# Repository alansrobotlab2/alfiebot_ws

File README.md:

# 🤖 Alfiebot Workspace

<div align="center">

**A ROS2 Jazzy workspace for an intelligent, interactive humanoid robot**

</div>

---

## 📋 Overview

Alfiebot is a conversational humanoid robot built on ROS2 Jazzy, featuring voice interaction, LLM-powered intelligence, and expressive servo-controlled movements. The platform integrates automatic speech recognition (ASR), large language model (LLM) processing, text-to-speech (TTS), and sophisticated motor control through micro-ROS firmware.

### Key Features

- 🎤 **Voice Interaction** - Real-time speech recognition and natural language understanding
- 🧠 **LLM Integration** - Powered by modern language models for intelligent conversations
- 🔊 **Text-to-Speech** - Natural voice synthesis for robot responses
- ⚙️ **Motor Control** - Servo-based articulation with Waveshare serial bus servos
- 📡 **Micro-ROS** - Efficient real-time communication with embedded firmware
- 🌐 **Network Management** - Built-in WiFi hotspot capabilities via Alfienet

---

## 🗂️ Package Structure

```
alfiebot_ws/
├── src/
│   ├── alfie_agent/       # High-level behavioral control and orchestration
│   ├── alfie_asr/         # Automatic speech recognition node
│   ├── alfie_back/        # Backend services and utilities
│   ├── alfie_bringup/     # Launch files and system startup configuration
│   ├── alfie_firmware/    # Micro-ROS firmware for embedded systems
│   ├── alfie_llm/         # Large language model integration
│   ├── alfie_mic/         # Microphone interface and audio capture
│   ├── alfie_msgs/        # Custom ROS2 message and service definitions
│   ├── alfie_tools/       # Development and debugging tools (servotool, etc.)
│   └── alfie_tts/         # Text-to-speech synthesis node
└── alfienet/              # WiFi hotspot and network management scripts
```

---

## 🚀 Quick Start

### Prerequisites

- NVIDIA Jetson device (tested on Jetson Orin series)
- ROS2 Jazzy
- Ubuntu 24.04 (JetPack 7)

### Setup

For detailed environment setup and dependencies, see **[SETUP.md](SETUP.md)**.

```bash
# Clone the repository
git clone https://github.com/alansrobotlab2/alfiebot_ws.git
cd alfiebot_ws

# Install dependencies
rosdep install --from-paths src --ignore-src -r -y

# Build the workspace
colcon build --symlink-install

# Source the workspace
source install/setup.zsh
```

### Running Alfiebot

```bash
# Launch the complete system
ros2 launch alfie_bringup alfiebot.launch.py

# Or launch individual components as needed
ros2 run alfie_asr asr_node
ros2 run alfie_llm llm_node
ros2 run alfie_tts tts_node
```

---

## 🛠️ Development Status

### Active Tasks

- [ ] Troubleshoot micro ros agent locking out usb when quitting launchfile
- [ ] Evaluate BEST_EFFORT vs RELIABLE QoS for core topics
- [ ] Debug message/video lag after overnight operation
- [ ] Investigate `alfie_mic` crash issue (related to reset step?)
- [ ] Benchmark Foxglove Bridge performance (on-device vs off-device)
- [ ] Fix ServoTool2 memory offset bug affecting EEPROM writes
- [ ] Add rate limiting to ServoTool slider (target: 20Hz)
- [ ] Implement min/max value constraints in ServoTool UI
- [ ] Add raw/degrees/radians unit selector to ServoTool I/O

### Modeling & Simulation

- [ ] Create simplified OnShape CAD model
- [ ] Export URDF for Foxglove Studio visualization
- [ ] Export model to NVIDIA Omniverse

### Hardware Development

- [ ] Build teleoperation rig with Teensy 4.2
- [ ] Implement "high five" gesture interaction

#### Upcoming Hardware Improvements

- [ ] Install dual antennas on head with body extensions
- [ ] Replace 6.6ft USB-C cable with 5ft version
- [ ] Upgrade shoulder bearings

#### Completed Hardware Updates ✅

- ✅ Installed smaller diameter middle wheel inserts (reduced turn jiggle)
- ✅ Replaced with quieter case fans in base
- ✅ Added wiring harness slack for 180° head rotation
- ✅ Centered Jetson for improved airflow

---

## 🔮 Future Roadmap

### Hardware Evolution

- **Base Redesign** - Lower-mounted drive wheels or omniwheel configuration
- **Autonomous Charging** - Docking station with automatic charge detection
- **Cable Management** - Cleaner internal wiring layout

### Software Enhancements

- Advanced behavioral planning and decision-making
- Multi-modal interaction (vision + voice)
- Cloud integration for knowledge updates
- Improved power management and battery monitoring

---

## 📚 Documentation

- **[SETUP.md](SETUP.md)** - Detailed installation and configuration guide
- **[Firmware README](src/alfie_firmware/README.md)** - Micro-ROS firmware documentation
- **[MKS-SERVO42C_1.0.md](MKS-SERVO42C_1.0.md)** - Servo motor documentation
- **[alfienet/](alfienet/)** - Network configuration documentation

---

## 🤝 Contributing

Contributions are welcome! This is an active research and development project.

---

## 📄 License

This project is licensed under the Apache License 2.0 - see the [LICENSE](LICENSE) file for details.

---

## 👤 Maintainer

**Alan's Robot Lab**  
📧 alansrobotlab@gmail.com  
🔗 [GitHub](https://github.com/alansrobotlab2)

---

<div align="center">
  <sub>Built with ❤️ and ROS2</sub>
</div>

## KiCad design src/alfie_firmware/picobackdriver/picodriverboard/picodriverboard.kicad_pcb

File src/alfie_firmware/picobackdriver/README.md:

# Pico Back Driver Board

Firmware for the Alfie robot's back lift — a belt-driven linear actuator on a
Waveshare RP2040 Zero, driven by a DRV8876 H-bridge and controlled over
micro-ROS.

Gen2 hardware. The gen1 TB6612FNG is gone; so is most of what the previous
revision of this document said about it.

---

## Hardware

| | |
|---|---|
| **MCU** | Waveshare RP2040 Zero (serial `5303284740EC7D9C` → `/dev/ttyAlfieB`) |
| **Driver** | DRV8876 (3.5 A, 44.3 °C/W, integrated current sense + fault reporting) |
| **Motor** | JGB37-520B, **56:1**, 178 rpm @ 12 V, 11 PPR quadrature encoder (fitted 2026-10-25, replacing the interim 90:1 / 110 rpm) |
| **Transmission** | 20T 2GT pulley (2 mm pitch, 40 mm circumference), GT2 belt |
| **IMU** | BNO085 on I2C0 |
| **Status LED** | WS2812B on GP16 |
| **Comms** | micro-ROS over USB CDC @ 1,000,000 baud |

### Pin map

| GPIO | Signal | Notes |
|---|---|---|
| GP28 | `EN` | PWM, 24 kHz |
| GP27 | `PH` | direction — `MOTOR_PH_UP = LOW` (56:1 motor) |
| GP26 | `PMODE` | driven **LOW** for PH/EN mode. Never leave floating |
| GP15 | `nSLEEP` | HIGH = active |
| GP7 | `nFAULT` | open-drain input, internal pull-up |
| GP3 / GP2 | `ENC_A` / `ENC_B` | quadrature, both on CHANGE |
| GP1 | `LIMIT_SW` | bottom limit, **normally closed → HIGH = triggered** |
| GP12 / GP13 | I2C0 SDA / SCL | BNO085 |
| GP11 | IMU reset | |
| GP16 | WS2812B | |

Free: GP0, GP4, GP5, GP6, GP8, GP9, GP10, GP14, GP17–22.

### DRV8876 configuration

| Pin | State | Why |
|---|---|---|
| `PMODE` | driven LOW from GP26 | PH/EN mode. Floating = independent half-bridge, which **inverts the down duty** on a gravity-loaded axis |
| `IMODE` | 20 kΩ to GND (level 2) | Only the overcurrent response still matters: **auto-retry**, not latch-off |
| `VREF` | tied to 3.3 V | Only needs to be above GND now |
| `IPROPI` / `CS` | **strapped to GND** | Disables internal current regulation, datasheet §7.3.3.2 |

**Current regulation is deliberately disabled.** The ITRIP chopper was clamping
below the current required to lift, so the actuator could not rise at any duty.
Overcurrent protection (3.5–5.5 A, 2 ms auto-retry) and thermal shutdown are
separate silicon and remain active — the part is still self-protecting.

With the chopper gone, **`VELOCITY_PID_OUTPUT_LIMIT` is the only thing bounding
motor current.** See `config.h`, "WHY THERE IS NO CURRENT TRIP".

---

## Calibrated constants

> **56:1 fitted 2026-10-25.** The constants below are the 56:1 values, rescaled
> from the 90:1 calibration by gearbox ratio. They are not yet confirmed on
> hardware. The performance table and its fit are 90:1 measurements. Re-run
> `position_test.cpp` calibration and the duty sweep, and verify encoder phasing
> and PH polarity by hand before the first powered move.

```
GEAR_RATIO              56.0        56:1 datasheet (90:1 calibrated to 90.1 against datasheet 90)
ENCODER_COUNTS_PER_METER 61,600     = 11 PPR × 4 × 56 / 0.040 m
counts per mm           61.6        350 mm = 21,560 counts
ACTUATOR_MAX_POSITION   0.350 m     real stroke from the limit switch
```

At 90:1, two independent checks agreed: the count calibration lands within 0.1% of the
geometric model, and the measured voltage-speed slope (5.82 mm/s per volt) is
within 5% of the theoretical 6.11 for 110 rpm through a 40 mm pulley.

### Measured performance (90:1)

At 56:1 the scaled fit is `v = 9.42 × (V_applied − 2.41)` mm/s: ~66 mm/s at
duty 200 and ~75 mm/s at duty 220, unmeasured.

| duty | speed (up) | 350 mm | stall current |
|---|---|---|---|
| 160 | 35.1 mm/s † | 10.0 s | 2.28 A |
| 200 | 46.1 mm/s | 7.7 s | 2.85 A |
| **220** ← ceiling | **51.5 mm/s** | **6.9 s** | 3.14 A |
| 245 | 58.4 mm/s † | 6.0 s | 3.50 A ← OCP floor |

† extrapolated from the measured fit `v = 5.82 × (V_applied − 1.50)` mm/s;
duty 200 and 220 are measured full-stroke runs.

Descent is gravity-assisted and ~35% faster: 69.7 mm/s at duty 220.

Running current is **~0.45 A** (from the voltage-speed intercept) — well under
the motor's 1.0 A continuous rating, and ~0.14 W in the driver. The drive is
lightly loaded.

The duty ceiling of 220 is set by **OCP margin**, not thermals: a dead stall
draws 3.14 A, 10% under the DRV8876's 3.5 A trip point, so a jam is answered by
the firmware stall detector rather than by driver retry chatter. 245 is the hard
ceiling on the ceiling.

---

## Control architecture

Dual-core, cascaded control.

- **Core 0** — peripherals: motor, encoder ISRs, IMU, limit switch, LED. Control
  loop at **500 Hz** (`CONTROL_LOOP_PERIOD_MS = 2`).
- **Core 1** — micro-ROS state machine at a drift-free **50 Hz**.

```
BackCmd.position ──► position error ──► × POSITION_KP (12) ──► desired velocity
                                                                      │
  BackCmd.velocity (a LIMIT) and √(2·a·|e|) braking curve ──► clamp ◄─┘
                                                     │
                            MAX_ACTUATOR_ACCELERATION ▼ ramp
                                                     │
                     encoder velocity ──► applyVelocityPID ──► PWM ──► DRV8876
```

**`BackCmd.velocity` is a maximum, not a setpoint.** Position is the command;
velocity and acceleration are constraints on how it gets there. Leaving either
at 0 means "use the maximum": GR00T's action publisher sends position only, and
before 2026-10-25 a 0 acceleration froze the ramp so the back never moved.

The braking curve caps speed at what the commanded acceleration can shed before
the target, so slow ramps (VR teleop uses 0.1 m/s²) land without overshoot.

Measured with GR00T-style position-only commands at 15 Hz (`POSITION_KP` 12,
1 mm tolerance): steps of 3-20 mm land within 0.1-0.7 mm in 0.12-0.54 s with no
overshoot; a 31 mm/s sine lags 2.3 mm on average (v / POSITION_KP); full strokes
take 7.3 s with under 0.7 mm overshoot.

### Gains and limits

```
VELOCITY_FF_UP_OFFSET       78        feedforward: up duty = 78 + 2.5 × v[mm/s] + friction
VELOCITY_FF_UP_GAIN         2500      counts per m/s
VELOCITY_FF_DOWN_OFFSET     -13       feedforward: down duty = -13 + 2.0 × v[mm/s] - friction (v < 0)
VELOCITY_FF_DOWN_GAIN       2000      counts per m/s
VELOCITY_FF_FRICTION_SLOPE  40        friction = 40 counts/m × (height − 0.160 m), opposing motion
VELOCITY_PID_KP             3000.0    PWM counts per m/s of error, trims the feedforward
VELOCITY_PID_KI             3000.0
VELOCITY_PID_KD             0.0       disabled
VELOCITY_PID_OUTPUT_LIMIT   220       duty ceiling = current ceiling
VELOCITY_PID_INTEGRAL_LIMIT 0.025     KI × limit = 75 counts of trim
MAX_ACTUATOR_VELOCITY       0.048 m/s measured on the 56:1
MAX_ACTUATOR_ACCELERATION   0.35 m/s²
MIN_PWM_UPWARD              100       floor, commanded direction only (re-measured on the 56:1)
MIN_PWM_DOWNWARD            20        gravity assists
POSITION_TOLERANCE_M        0.001     brake inside this
POSITION_KP                 12.0      outer loop gain (1/s)
```

Feedforward carries the load (56:1 tune, 2026-10-25); the PID only trims it.
Friction rises with height in both directions (repeatable, ~±5 counts across
the stroke), so the feedforward includes a height term. Velocity is the count
difference over a 20 ms window timed in `micros()`.

⚠️ **The load drifts warm.** After ~2 h of cycling the same speeds needed ~30
more counts of duty (board 41 → 50 °C, motor and gearbox warm), and 48 mm/s up
pinned at the 220 ceiling. The feedforward was fitted cool; the integral absorbs
up to 75 counts of drift.
Step response 20-48 mm/s up and down: rise 240-450 ms, steady-state error
within ±1.5%, 2-5% ripple. A full 0 -> 340 mm stroke takes 8.2 s.

Inside `POSITION_TOLERANCE_M` with the ramp at rest the bridge simply brakes
(the short brake holds the 56:1 with no measurable sag). Before that, encoder
noise was floored into continuous +100 / -20 pulses at every hold. Floors apply
only in the commanded direction, and the integral resets when it flips.

---

## Safety

| Detector | Trips on | Recovery |
|---|---|---|
| **Stall** | duty above `STALL_PWM_THRESHOLD` with no motion for 250 ms (500 ms before the first motion of a move — break-away) | Classified: `MOTOR_BLOCKED` (was moving, then stopped) hard-latches immediately; `LOAD_EXCEEDED` (never broke away) retries 3× at 3 s intervals then latches |
| **Runaway** | over 0.080 m/s, or motion against the command for 150 ms | Latches until reset — miswiring cannot be retried away |
| **nFAULT** | debounced low | Real device fault only (OCP/TSD/UVLO); chopping is disabled. Re-arms via nSLEEP cycle, rate-limited to 1/s |
| **Calibration** | see below | Own guards, because the usual two cannot fire on that path |

Runaway hard-latches because it means the hardware is not what the firmware
believes it to be — and on a gravity-loaded axis a sign inversion becomes
positive feedback.

### Error codes (`BackState.error_code`)

| | |
|---|---|
| `0x00` | none |
| `0x02` | motor driver fault |
| `0x08` | `DRIVER_FAULT` — nFAULT asserted |
| `0x09` | `MOTOR_BLOCKED` — obstruction, hard latched |
| `0x0A` | `LOAD_EXCEEDED` — never broke away, retrying |
| `0x0B` | `MOTOR_RUNAWAY` — overspeed or wrong direction, latched |

`stall_position` and `stall_count` are published alongside. A real obstruction
stalls at the **same** `stall_position` across retries; an overload stalls
wherever it happened to start.

---

## Status LED (WS2812B)

Faults take priority over everything else.

| Colour | State |
|---|---|
| **Fast red strobe** (80 ms) | Runaway — most severe, needs a reset |
| **Solid red** | Obstruction hard-latched, or driver fault |
| **Blinking red** (250 ms) | Overload, retrying on its own |
| **Purple** (pulsing) | Calibration in progress |
| **Dim blue** | Waiting for micro-ROS agent |
| **Yellow** | Agent connected, creating entities |
| **Cyan** | Moving |
| **Green heartbeat** | Operational and idle |
| **Orange** | Agent disconnected |
| **Dim white** | Unknown state |

Solid vs blinking red is the distinction that matters when you are looking at
the robot rather than at a topic: solid needs a human, blinking will retry.

---

## ROS 2 interface

Node `back_drive_controller` in namespace **`/alfie/low`**.

### Topics

| Topic | Type | Dir | QoS | Rate |
|---|---|---|---|---|
| `/alfie/low/backcmd` | `alfie_msgs/BackCmd` | sub | Best Effort | on demand |
| `/alfie/low/backstate` | `alfie_msgs/BackState` | pub | Best Effort | 50 Hz |
| `/alfie/low/neck_power` | `std_msgs/Empty` | sub | Best Effort | heartbeat |

**Best Effort throughout** — for real-time motor control, stale data is worse
than a dropped message. A `RELIABLE` subscriber on the host side will simply
never match and will sit silent.

`BackState` carries position, velocity, acceleration, encoder pulses, PWM
output, limit switch state, board temperature, calibration status, the fault
fields above, and the BNO085 IMU data.

### Service

| Service | Type | QoS |
|---|---|---|
| `/alfie/low/calibrate_back` | `alfie_msgs/srv/BackRequestCalibration` | Reliable |

---

## Calibration (homing)

Homes to the bottom limit switch and zeroes position. **Required before any
position command is meaningful** — without it, every position is measured
against an arbitrary origin.

```bash
ros2 service call /alfie/low/calibrate_back alfie_msgs/srv/BackRequestCalibration
```

**Sequence:**

1. Rejects the call if calibration is already running.
2. Blocks incoming `BackCmd` for the duration.
3. Reads the limit switch — **HIGH = triggered** (normally-closed).
4. If not already at the bottom, drives down at a fixed `CALIBRATION_PWM` (80)
   while polling the switch and the encoder. From the top of the stroke that is
   ~25 mm/s and ~13.5 s, inside the 20 s timeout. 60 was too close to where
   gravity balances friction: on a stiff day it averaged 15 mm/s and timed out.
5. On assertion: immediate brake, encoders reset, PID state cleared,
   `is_calibrated` set.

**This path carries its own guards**, because the usual ones cannot fire on it:
it drives the bridge directly with normal motor control suspended, so
`motor.pwm_output` is stale — runaway detection is skipped explicitly, and stall
detection silently never triggers.

| Guard | Threshold | Result |
|---|---|---|
| Stall | no 20 counts of progress within 400 ms | abort, `success: false` |
| Reversal | 200 counts *upward* while commanded down | latches `runaway_detected` — this is a wiring fault and must not be retried |
| Timeout | 20 s | abort, `success: false` |

Before these existed, a failed homing run drove into the bottom stop for the
full 20 s at the duty ceiling with no current limit behind it.

---

## Building and flashing

```bash
~/.platformio/penv/bin/pio run -e back              # build
~/.platformio/penv/bin/pio run -e back -t upload    # flash
```

After changing a `.msg`, clean the micro-ROS build first:

```bash
~/.platformio/penv/bin/pio run -e back -t clean_microros
```

Install the udev rule so the board appears as `/dev/ttyAlfieB`:

```bash
sudo cp ../99-alfie-pico.rules /etc/udev/rules.d/
sudo udevadm control --reload-rules && sudo udevadm trigger
```

⚠️ **`pio run | tail` reports `tail`'s exit code.** A build can fail while the
shell reports success. Check the output, not the status.

---

## Bring-up tools

In [`bringup/`](bringup/) — not compiled, since PlatformIO only builds `src/`
and `lib/`. See [`bringup/README.md`](bringup/README.md).

- **`position_test.cpp`** — open-loop position moves and `GEAR_RATIO`
  calibration. This is what produced the constants above.
- **`pid_tune.py`** — velocity-PID step-response harness. Reports steady-state
  error, rise time, overshoot, settling, ripple, and time spent pinned at the
  duty ceiling or the PWM floor.

---

## Code structure

```
├── include/
│   ├── config.h              # All constants, heavily annotated with WHY
│   └── driverboard.h         # DriverBoard class and state structs
├── lib/
│   ├── motor_control/        # Motor, encoder, safety detectors, LED
│   ├── ros_interface/        # micro-ROS entities, calibration service
│   └── ws2812/               # PIO-based RGB LED driver
├── src/
│   └── main.cpp              # Dual-core entry points
├── bringup/                  # Hardware bring-up tools (not compiled)
└── extra_packages/
    └── alfie_msgs/           # Custom ROS 2 messages
```

`config.h` is the primary reference. It records the reasoning behind each
constant, including dead ends, so they are not re-explored.

---

## Known limitations

- **`ACTUATOR_MAX_POSITION` = 0.350 has almost no margin.** The measured stroke
  is 350 mm and **there is no top limit switch** — only the bottom is switched.
  Nothing stops an overrun except the stall detector, after it has been pushing
  into the stop. 0.340 would be cheap insurance.
- **`MIN_PWM_UPWARD` was measured with the broken encoder decoder** (see below)
  and may be conservative. Re-measuring could widen the 2.5:1 controllable speed
  range considerably.
- **No current measurement anywhere in the system** — IPROPI is grounded. Load is
  inferred from the voltage-speed relationship, not measured.

### Bugs fixed during gen2 bring-up

Recorded because each was live in the shipping firmware and none announced
itself:

- **Encoder decoder** counted ±1 on every interrupt from current pin levels with
  no state memory, losing ~1 count in 3 and drifting cumulatively (20 mm after
  one round trip, 32 mm after two). It corrupted *every* calibration this
  project ever took, including gen1's, and is the origin of the long-standing
  "unexplained 2.33× gap". Replaced with a Gray-code transition table.
- **Limit switch polarity** inverted at all three read sites, which made
  calibration skip its descent and zero wherever the actuator happened to be — a
  silent false datum with no error and no timeout.
- **`RUNAWAY_VELOCITY_MPS`** derived as `MAX_ACTUATOR_VELOCITY × 2`, which sat
  below real gravity-assisted descent speeds. Every normal descent would have
  latched an unrecoverable fault. Now an absolute constant.

---

## Coding standards

1. Descriptive names; comments explain *why*, not *what*.
2. Constants in `config.h`, with the reasoning beside them.
3. **No serial prints** — the port is micro-ROS's.
4. Test on hardware. Every constant above that says "measured" was.
5. Keep this README current with the code.

## Resources

- [DRV8876 datasheet](https://www.ti.com/lit/ds/symlink/drv8876.pdf)
- [Arduino-Pico / PlatformIO](https://arduino-pico.readthedocs.io/en/latest/platformio.html)

## Authors

Alfie Bot Project

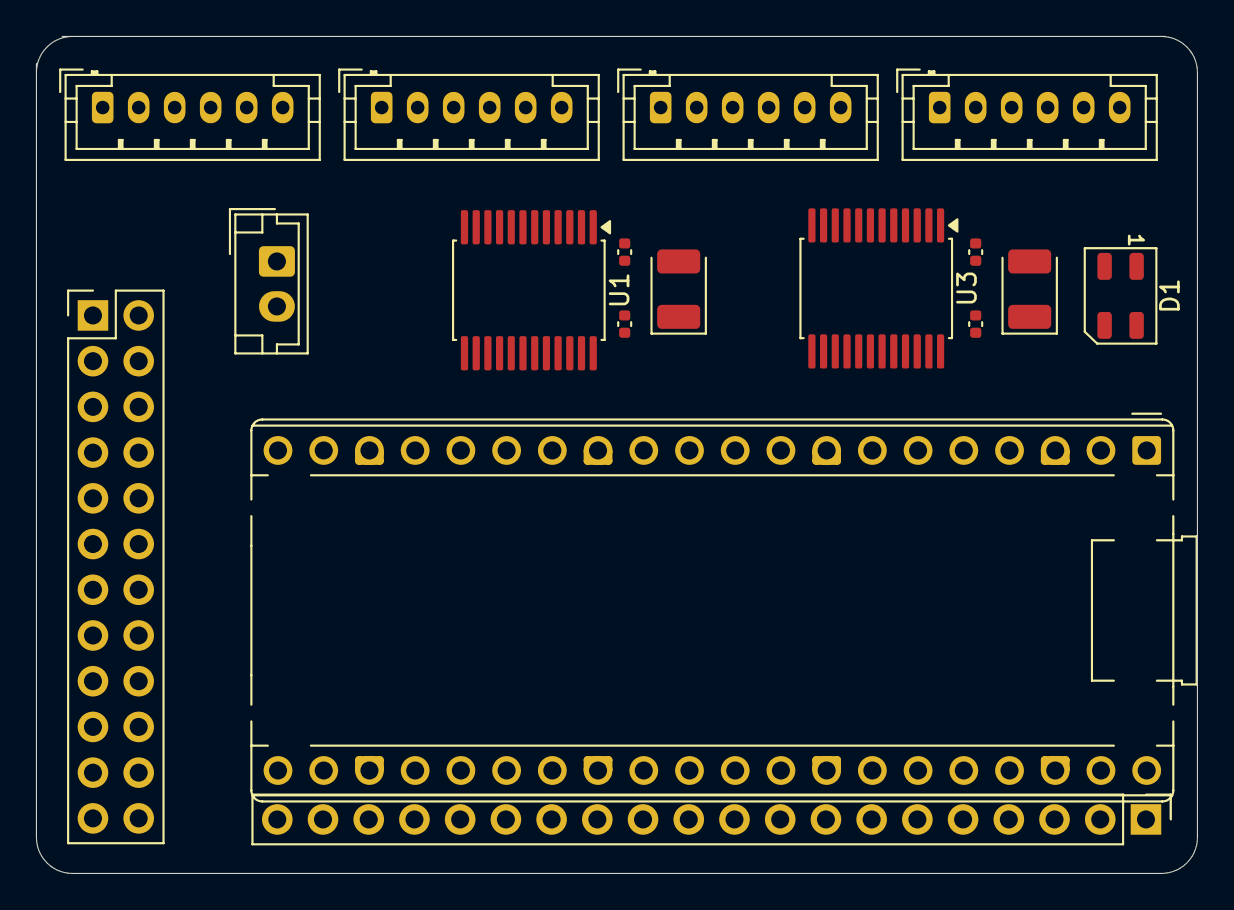
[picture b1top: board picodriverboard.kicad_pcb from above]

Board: 4 copper layers, 64.5 x 46.5 mm, 17 parts (0 on the bottom side), 11 nets.

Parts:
A1: RaspberryPi_Pico; RaspberryPi_Pico_Common_THT
C1, C2, C4, C6: 0.1uF; C_0402_1005Metric
C3, C5: 10uF; CP_EIA-3528-12_Kemet-T
D1: WS2812B; LED_WS2812B-Mini_PLCC4_3.5x3.5mm
J1: PH 2.0 6P MotorA; JST_PH_B6B-PH-K_1x06_P2.00mm_Vertical
J2: PH 2.0 6P MotorB; JST_PH_B6B-PH-K_1x06_P2.00mm_Vertical
J3: PH 2.0 6P MotorC; JST_PH_B6B-PH-K_1x06_P2.00mm_Vertical
J4: PH 2.0 6P MotorD; JST_PH_B6B-PH-K_1x06_P2.00mm_Vertical
J5: Conn_01x02_Socket; JST_EH_B2B-EH-A_1x02_P2.50mm_Vertical
J6: Conn_02x12_Top_Bottom; PinHeader_2x12_P2.54mm_Vertical
J7: Conn_01x20_Socket; PinHeader_1x20_P2.54mm_Vertical
U1, U3: TB6612FNG; SSOP-24_5.3x8.2mm_P0.65mm

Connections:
A01: J1.1, U1.1 (A01@1), U1.2 (A01@2)
A02: J1.6, U1.5 (A02@5), U1.6 (A02@6)
B01: J2.1, U1.11 (B01@11), U1.12 (B01@12)
B02: J2.6, U1.7 (B02@7), U1.8 (B02@8)
C01: J3.1, U3.1 (A01@1), U3.2 (A01@2)
C02: J3.6, U3.5 (A02@5), U3.6 (A02@6)
D01: J4.1, U3.7 (B02@7), U3.8 (B02@8)
D02: J4.6, U3.11 (B01@11), U3.12 (B01@12)
GND: A1.3 (GND), A1.8 (GND), A1.13 (GND), A1.18 (GND), A1.23 (GND), A1.28 (GND), A1.38 (GND), C1.2, C2.2, C4.2, C6.2, J1.2, J2.2, J3.2, J4.2, J5.2, U1.3 (PGND1@3), U1.4 (PGND1@4), U1.9 (PGND2@9), U1.10 (PGND2@10), U1.18 (GND), U3.3 (PGND1@3), U3.4 (PGND1@4), U3.9 (PGND2@9), U3.10 (PGND2@10), U3.18 (GND)
VCC: A1.36 (3V3), C2.1, C6.1, J1.3, J2.3, J3.3, J4.3, U1.20 (VCC), U3.20 (VCC)
VM: C1.1, C4.1, J5.1, U1.13 (VM2), U1.14 (VM3), U1.24 (VM1), U3.13 (VM2), U3.14 (VM3), U3.24 (VM1)

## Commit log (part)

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2025-12-31 fixed rosbag record
2025-12-31 some more tweaks for capturing episodes
2025-12-31 lower voice a bit, add settings for speed and playback freq or pitch
2025-12-31 captuer more topics, refactor teleop arm viz, set sane accel and vel values for twist for base
2026-01-01 start filling out gr00t meta files etc, clean up parakeet asr
2026-01-01 first pass at conversion script
2026-01-01 multi theaded rosbag to groot
2026-01-01 gr00t format changes
2026-01-01 tune asr; max utterance 15 seconds, remove robotlowcmd warning
2026-01-02 lil parakeet cleanup.
2026-01-03 refine bringup state capture and rosbag
2026-01-04 starting work on the client
2026-01-04 parakeet asr fix for pytorch-gpu
2026-01-04 capture back joint in state and action
2026-01-06 cascade changes for addition of back joint
2026-01-10 parakeet asr works offline
2026-01-10 fix alfienet, wifi watchdog, video to 15 fps
2026-01-16 alfie_vr cleanup; master_cmd fix
2026-01-19 gr00t scenario capture updates
2026-01-25 alie groot server standalone script
2026-01-25 tweaks to client and server
2026-01-25 gr00t updates
2026-01-25 moar fixes
2026-01-25 server
2026-01-25 fiixes
2026-01-25 fiewa
2026-02-01 fixed info.json
2026-02-01 fix rosbag converter
2026-02-01 training and inference updates
2026-02-02 add replay mode to gr00t client and server
2026-02-02 inference fix
2026-02-02 server episode replay logging
2026-02-02 server fix
2026-02-02 server fix 2
2026-02-03 troubleshooting replay
2026-02-03 modality update, rosbag to groot no longer generate stats
2026-02-03 fine tune updates
2026-02-06 groot open loop eval now reports similar MSE MAE to open loop eval with alfie groot client server zmq comms.
2026-02-06 initial support for executing all 16 actions per chunk
2026-02-06 add groot server visualizer
2026-02-06 logging for client server troubleshooting
2026-02-07 alfie config to absolute
2026-02-07 groot server gradio fixes
2026-02-07 gr00t troubleshooting
2026-02-07 groot server fix
2026-02-07 fix groot server ping
2026-02-07 fix video config for fine tuning pipeline
2026-02-08 add initial back height to groot client config
2026-02-08 troubleshooting live vs recording video feeds
2026-02-09 episode manager improvements
2026-02-10 client server pipeline supports raw observation images
2026-02-10 fixes to pipeline
2026-02-10 groot open loop eval tweak
2026-02-10 remove joint limits, delta limits, handled in hardware
2026-02-10 we are executing the behaviors yay
2026-02-10 closer. current client tuning overshoots on can approach.
2026-02-14 first successful configuration, very jerky but works
2026-02-14 testing run 10
2026-02-14 Testing Run 12
2026-02-14 Testing Run 13
2026-02-14 Testing Run 14
2026-02-14 Testing Run 15
2026-02-14 Testing Run 16
2026-02-14 Testing Run 17
2026-02-14 Testing Run 19
2026-02-14 client server reference implmentation
2026-02-14 mino fixes for groot open loop eval
2026-02-14 reference implementation updates
2026-02-14 Test run 21
2026-02-14 groot server needs to exit gracefully with ctl c
2026-02-14 TEsting Run 22
2026-02-14 Testing Run 23
2026-02-14 Testing Run 24
2026-02-14 Testing Run 25
2026-02-14 Testing Run 26
2026-02-14 Testing Run 27
2026-02-14 Testing Run 28
2026-02-14 Testing Run 29
2026-02-14 Testing Run 30
2026-02-16 alfiebot config action horizon to 4
2026-02-16 inference server optimizations
2026-02-16 Testing Run 31
2026-02-16 more analysis
2026-02-16 client server analysis results.
2026-02-16 client server changes from analysis
2026-02-16 base_velocity_decay removed no longer needed
2026-02-16 capturing progress
2026-02-17 log actions and chunk ids
2026-02-17 executing all 16 steps raises safety check error
2026-02-17 consolidate using new chunk for base and joints
2026-02-17 pogos in arm push can out of the way
2026-02-17 commit before smoothing explorations
2026-02-17 smoothing analysis analysis
2026-02-17 groot server does a mock inference to trigger torch.compile --torch-compile
2026-02-17 second order action smoothing experiments
2026-02-17 last minute adjustment, drive very jerky
2026-02-17 gr00t reference implementation smoothing for client server
2026-02-19 client fixes
2026-02-19 groot client and server optimizations
2026-02-19 additional groot open loop eval diagnostics
2026-02-19 tweaks to improve inference speeds.
2026-02-19 15hz observations and async action packets
2026-02-19 groot replay eval with all options from groot client
2026-02-19 implemented full pipelining, 174ms per inference
2026-02-19 pipelined async comms now at 184
2026-02-19 revert back to 174ms server code
2026-02-20 optimal smoothing per claude testing
2026-02-20 now approach can better.
2026-02-20 attempt to reduce oscillations in joints
2026-02-22 ensemble sampling characterization
2026-02-22 update action smoothing md
2026-02-22 initial implementation of RTC for motion smoothing.
2026-02-22 initial implementation of deadband filtering
2026-02-22 test changes with groot replay eval

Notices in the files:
README.md:
License: Apache 2.0
